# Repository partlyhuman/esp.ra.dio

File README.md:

# ESP.Ra.Dio

An ESP32 Bluetooth LE joystick for Neo Geo + BlueRetro and anyone else!

In development.

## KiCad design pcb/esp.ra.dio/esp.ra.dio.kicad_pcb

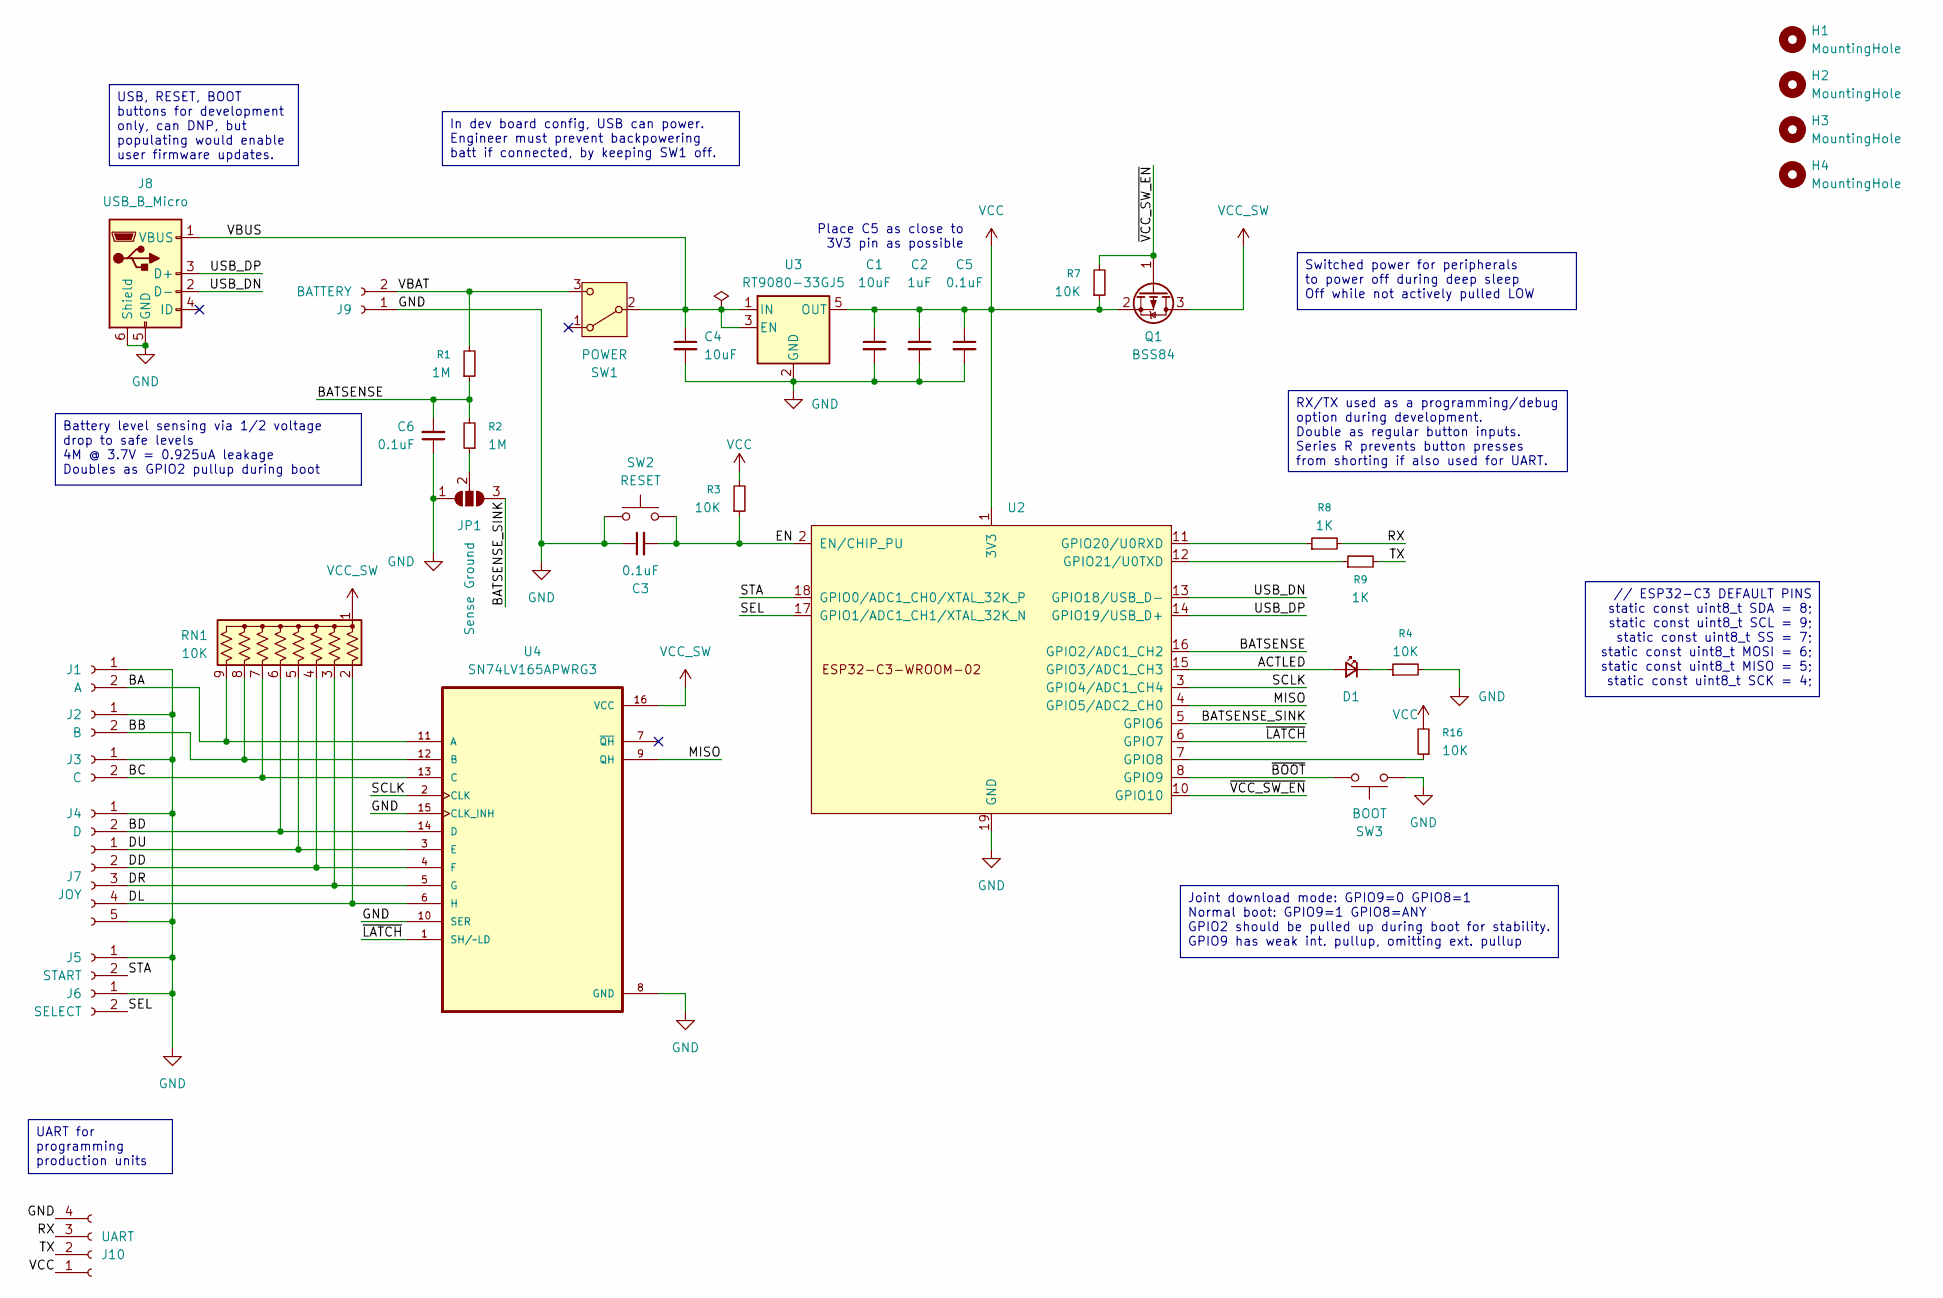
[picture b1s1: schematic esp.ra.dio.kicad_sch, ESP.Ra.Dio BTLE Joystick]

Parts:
C1, C4: 10uF; C_0805_2012Metric_Pad1.18x1.45mm_HandSolder
C2: 1uF; C_0805_2012Metric_Pad1.18x1.45mm_HandSolder
C3, C5, C6: 0.1uF; C_0805_2012Metric_Pad1.18x1.45mm_HandSolder
D1: ACTLED; LED_D3.0mm_Horizontal_O1.27mm_Z6.0mm
H1, H2, H3, H4: MountingHole; MountingHole_2.2mm_M2
J1: A; JST_XH_B2B-XH-A_1x02_P2.50mm_Vertical
J2: B; JST_XH_B2B-XH-A_1x02_P2.50mm_Vertical
J3: C; JST_XH_B2B-XH-A_1x02_P2.50mm_Vertical
J4: D; JST_XH_B2B-XH-A_1x02_P2.50mm_Vertical
J5: START; JST_XH_B2B-XH-A_1x02_P2.50mm_Vertical
J6: SELECT; JST_XH_B2B-XH-A_1x02_P2.50mm_Vertical
J7: JOY; JST_XH_B5B-XH-A_1x05_P2.50mm_Vertical
J8: USB_B_Micro; USB_Micro-B_Amphenol_10118193-0002LF_Horizontal
J9: BATTERY; JST_PH_B2B-PH-K_1x02_P2.00mm_Vertical
J10: UART; PinHeader_1x04_P2.54mm_Vertical
JP1: Sense Ground; SolderJumper-3_P1.3mm_Open_Pad1.0x1.5mm_NumberLabels
Q1: BSS84; SOT-23
R1, R2: 1M; R_0805_2012Metric_Pad1.20x1.40mm_HandSolder
R3, R4, R7, R16: 10K; R_0805_2012Metric_Pad1.20x1.40mm_HandSolder
R8, R9: 1K; R_0805_2012Metric_Pad1.20x1.40mm_HandSolder
RN1: 10K; RN
SW1: POWER; SW_Slide_SPDT_Angled_CK_OS102011MA1Q
SW2: RESET; SW_SPST_PTS810
SW3: BOOT; SW_SPST_PTS810
U2: VCC; ESP32-C3-WROOM-02
U3: RT9080-33GJ5; SOT-23-5
U4: SN74LV165APWRG3; SOP65P640X120-16N; DigiKey_Part_Number 296-31867-1-ND

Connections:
/ACTLED: D1.2 (A), U2.15 (GPIO3/ADC1_CH3)
/BA: J1.2, RN1.9 (R8), U4.11 (A)
/BATSENSE: C6.2, R1.1, R2.2, U2.16 (GPIO2/ADC1_CH2)
/BATSENSE_SINK: JP1.3 (B), U2.5 (GPIO6)
/BB: J2.2, RN1.8 (R7), U4.12 (B)
/BC: J3.2, RN1.7 (R6), U4.13 (C)
/BD: J4.2, RN1.6 (R5), U4.14 (D)
/DD: J7.2, RN1.4 (R3), U4.4 (F)
/DL: J7.4, RN1.2 (R1), U4.6 (H)
/DR: J7.3, RN1.3 (R2), U4.5 (G)
/DU: J7.1, RN1.5 (R4), U4.3 (E)
/EN: C3.2, R3.1, SW2.1, U2.2 (EN/CHIP_PU)
/MISO: U2.4 (GPIO5/ADC2_CH0), U4.9 (QH)
/RX: J10.3, R8.2
/SCLK: U2.3 (GPIO4/ADC1_CH4), U4.2 (CLK)
/SEL: J6.2, U2.17 (GPIO1/ADC1_CH1/XTAL_32K_N)
/STA: J5.2, U2.18 (GPIO0/ADC1_CH0/XTAL_32K_P)
/TX: J10.2, R9.2
/USB_DN: J8.2 (D-), U2.13 (GPIO18/USB_D-)
/USB_DP: J8.3 (D+), U2.14 (GPIO19/USB_D+)
/VBAT: J9.2, R1.2, SW1.3 (C)
/VBUS: C4.1, J8.1 (VBUS), SW1.2 (B), U3.1 (IN), U3.3 (EN)
/~BOOT: SW3.1, U2.8 (GPIO9)
/~LATCH: U2.6 (GPIO7), U4.1 (SH/~LD)
/~VCC_SW_EN: Q1.1 (G), R7.2, U2.10 (GPIO10)
GND: C1.2, C2.2, C3.1, C4.2, C5.2, C6.1, J1.1, J2.1, J3.1, J4.1, J5.1, J6.1, J7.5, J8.5 (GND), J8.6 (Shield), J9.1, J10.4, JP1.1 (A), R4.2, SW2.2, SW3.2, U2.9 (GND), U2.19 (GND), U3.2 (GND), U4.8 (GND), U4.10 (SER), U4.15 (CLK_INH)
unnamed: D1.1 (K), R4.1
unnamed: JP1.2 (C), R2.1
unnamed: R16.1, U2.7 (GPIO8)
unnamed: R8.1, U2.11 (GPIO20/U0RXD)
unnamed: R9.1, U2.12 (GPIO21/U0TXD)
VCC: C1.1, C2.1, C5.1, J10.1, Q1.2 (S), R3.2, R7.1, R16.2, U2.1 (3V3), U3.5 (OUT)
VCC_SW: Q1.3 (D), RN1.1 (common), U4.16 (VCC)

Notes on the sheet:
Place C5 as close to 3V3 pin as possible
RX/TX used as a programming/debug option during development. Double as regular button inputs. Series R prevents button presses from shorting if also used for UART.
Battery level sensing via 1/2 voltage drop to safe levels 4M @ 3.7V = 0.925uA leakage Doubles as GPIO2 pullup during boot
USB, RESET, BOOT buttons for development only, can DNP, but populating would enable user firmware updates.
Joint download mode: GPIO9=0 GPIO8=1 Normal boot: GPIO9=1 GPIO8=ANY GPIO2 should be pulled up during boot for stability. GPIO9 has weak int. pullup, omitting ext. pullup
In dev board config, USB can power. Engineer must prevent backpowering batt if connected, by keeping SW1 off.
// ESP32-C3 DEFAULT PINS static const uint8_t SDA = 8; static const uint8_t SCL = 9; static const uint8_t SS = 7; static const uint8_t MOSI = 6; static const uint8_t MISO = 5; static const uint8_t SCK = 4;
UART for programming production units
Switched power for peripherals to power off during deep sleep Off while not actively pulled LOW

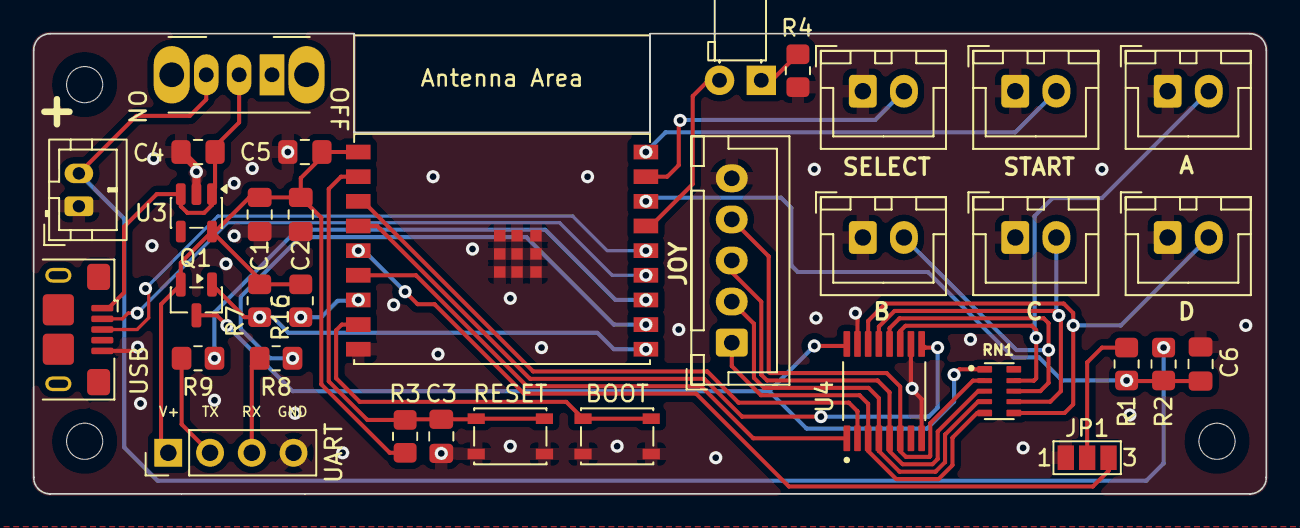
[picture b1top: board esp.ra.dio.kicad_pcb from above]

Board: 2 copper layers, 75.0 x 28.0 mm, 38 parts (0 on the bottom side), 33 nets.

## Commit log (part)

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2026-02-08 Fork from ng2040
2026-02-08 working coin in
2026-02-08 super-mini symbol/footprint
2026-02-08 Deep Sleep
2026-02-08 That was easy
2026-02-08 Some refactors to simplify
2026-02-08 Remove stuff we won't need and updating readme etc
2026-02-16 Updated layout that keeps LED and switch
2026-03-07 Enough dev boards, redo with WROOM
2026-03-07 Clear out old NG2040 designs
2026-03-08 Routing checkpoint
2026-03-08 Fix EN needs pullup
2026-03-08 Removes USB power, diode drop would have eaten into battery life too much
2026-03-20 Add activity LED, add weak pullups to strapping pins 2 and 8
2026-03-20 Comments and cleanup of routing
2026-03-21 Fix strapping pins, move buttons doubling with strapping pins to TX/RX
2026-03-24 oops backwards text
2026-06-01 PCB rev fixing do-nothing misplaced resistors
2026-06-01 Attempting to get this working with the PCB
2026-06-07 Build issues on c3 wroom
2026-06-07 PCB fixes, need to ensure better ground for ldo
2026-06-07 Get rid of USB R0s
2026-06-14 Re-splitting RX/BA nets
2026-06-14 Schematic: Bat sense
2026-06-19 WIP trying to handle oddities of ESP32C3 WROOM, give control over pairing, improve pairing with MiSTeR
2026-06-19 WIP converting PCB to use shift register
2026-06-21 Reverting to complete stock and the issue was really just with old binds?
2026-06-21 Rev4 PCB migrating to shift register, needs new layout
